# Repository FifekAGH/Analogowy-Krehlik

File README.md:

# Wstępny podział 

Krzysztof - frontend

Dominik - STM32F3 + decoupling, pullupy/downy itp

Filip - LDO, Układ odwracający napięcie, USB,Diody LED :)

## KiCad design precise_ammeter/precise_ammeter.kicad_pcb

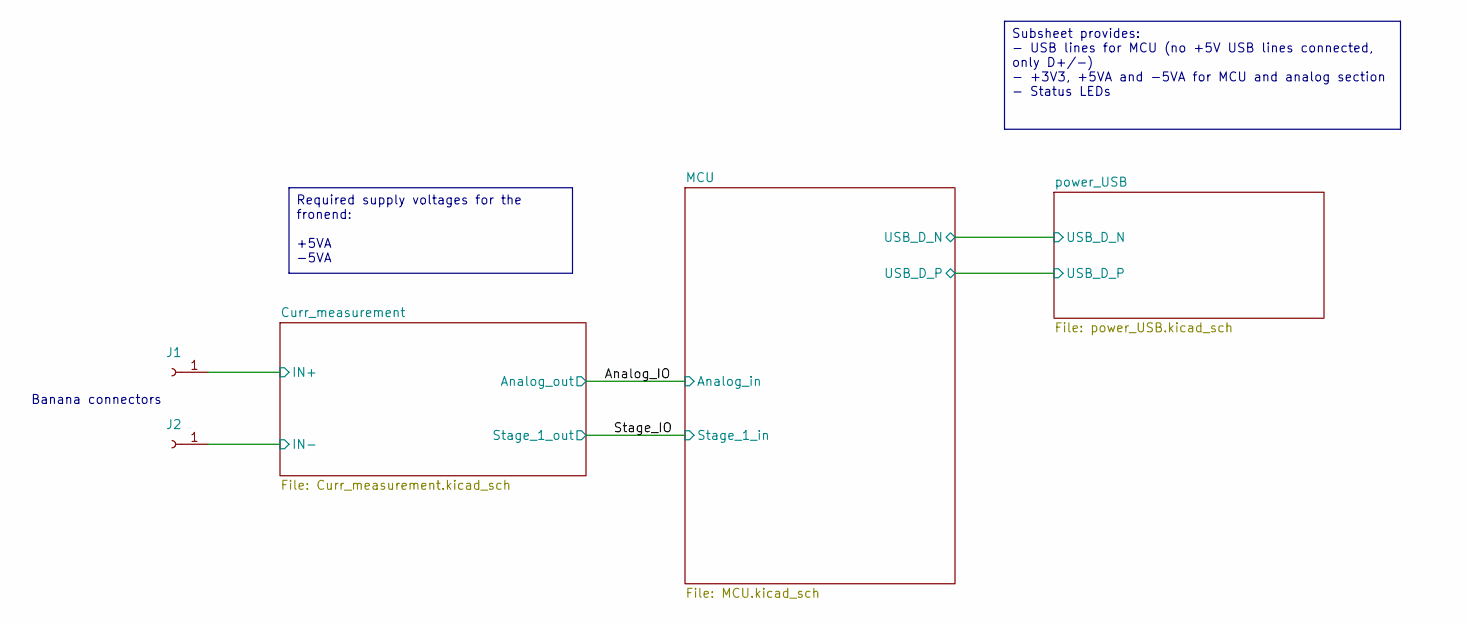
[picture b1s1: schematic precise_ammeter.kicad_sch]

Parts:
J1, J2: Conn_01x01_Socket; Banana_Jack_1Pin

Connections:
/Curr_measurement/IN+: J1.1; also elsewhere on the board
/Curr_measurement/IN-: J2.1; also elsewhere on the board

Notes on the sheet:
Banana connectors
Required supply voltages for the fronend: +5VA -5VA
Subsheet provides: - USB lines for MCU (no +5V USB lines connected, only D+/-) - +3V3, +5VA and -5VA for MCU and analog section - Status LEDs

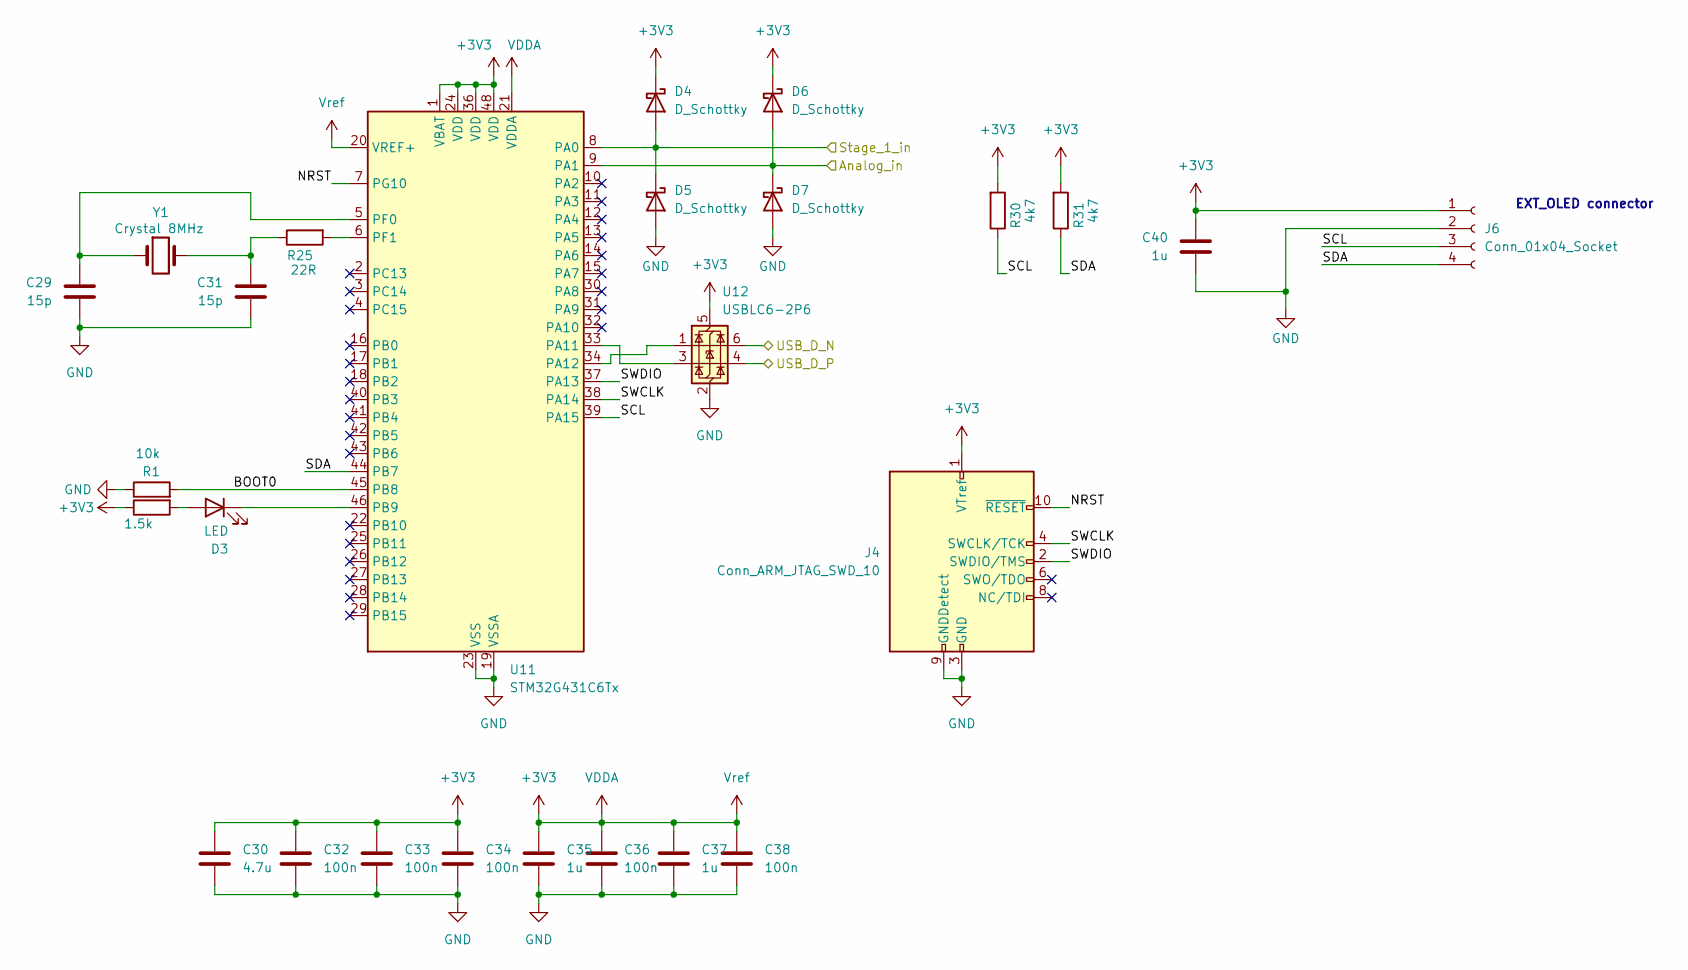
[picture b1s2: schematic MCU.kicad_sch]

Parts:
C29, C31: 15p; C_0805_2012Metric
C30: 4.7u; C_0805_2012Metric
C32, C33, C34, C36, C38: 100n; C_0805_2012Metric
C35, C37, C40: 1u; C_0805_2012Metric
D3: LED; LED_0805_2012Metric
D4, D5, D6, D7: D_Schottky; D_SOD-123F
J4: Conn_ARM_JTAG_SWD_10; PinHeader_2x05_P1.27mm_Vertical
J6: Conn_01x04_Socket; PinSocket_1x04_P2.54mm_Vertical
R1: 10k; R_0805_2012Metric_Pad1.20x1.40mm_HandSolder
R5: 1.5k; R_0805_2012Metric_Pad1.20x1.40mm_HandSolder
R25: 22R; R_0805_2012Metric_Pad1.20x1.40mm_HandSolder
R30, R31: 4k7; R_0805_2012Metric_Pad1.20x1.40mm_HandSolder
U11: STM32G431C6Tx; LQFP-48_7x7mm_P0.5mm
U12: USBLC6-2P6; SOT-666
Y1: Crystal 8MHz; Crystal_SMD_HC49-SD

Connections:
+3V3: C30.1, C32.1, C33.1, C34.1, C35.1, C36.1, C37.1, C38.1, C40.1, D4.1 (K), D6.1 (K), J4.1 (VTref), J6.1, R5.1, R30.2, R31.2, U11.1 (VBAT), U11.20 (VREF+), U11.21 (VDDA), U11.24 (VDD), U11.36 (VDD), U11.48 (VDD), U12.5 (VBUS); also elsewhere on the board
/Analog_IO: D6.2 (A), D7.1 (K), U11.9 (PA1); also elsewhere on the board
/MCU/BOOT0: R1.2, U11.45 (PB8)
/MCU/NRST: J4.10 (~RESET), U11.7 (PG10)
/MCU/SCL: J6.3, R30.1, U11.39 (PA15)
/MCU/SDA: J6.4, R31.1, U11.44 (PB7)
/MCU/SWCLK: J4.4 (SWCLK/TCK), U11.38 (PA14)
/MCU/SWDIO: J4.2 (SWDIO/TMS), U11.37 (PA13)
/MCU/USB_D_N: U12.6 (I/O1); also elsewhere on the board
/MCU/USB_D_P: U12.4 (I/O2); also elsewhere on the board
/Stage_IO: D4.2 (A), D5.1 (K), U11.8 (PA0); also elsewhere on the board
GND: C29.2, C30.2, C31.2, C32.2, C33.2, C34.2, C35.2, C36.2, C37.2, C38.2, C40.2, D5.2 (A), D7.2 (A), J4.3 (GND), J4.5 (GND), J4.9 (GNDDetect), J6.2, R1.1, U11.19 (VSSA), U11.23 (VSS), U11.35 (VSS), U11.47 (VSS), U12.2 (GND); also elsewhere on the board
unnamed: C31.1, R25.1, Y1.2
unnamed: D3.2 (A), R5.2
unnamed: D3.1 (K), U11.46 (PB9)
unnamed: U11.33 (PA11), U12.3 (I/O2)
unnamed: U11.34 (PA12), U12.1 (I/O1)
unnamed: C29.1, U11.5 (PF0), Y1.1
unnamed: R25.2, U11.6 (PF1)

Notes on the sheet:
EXT_OLED connector

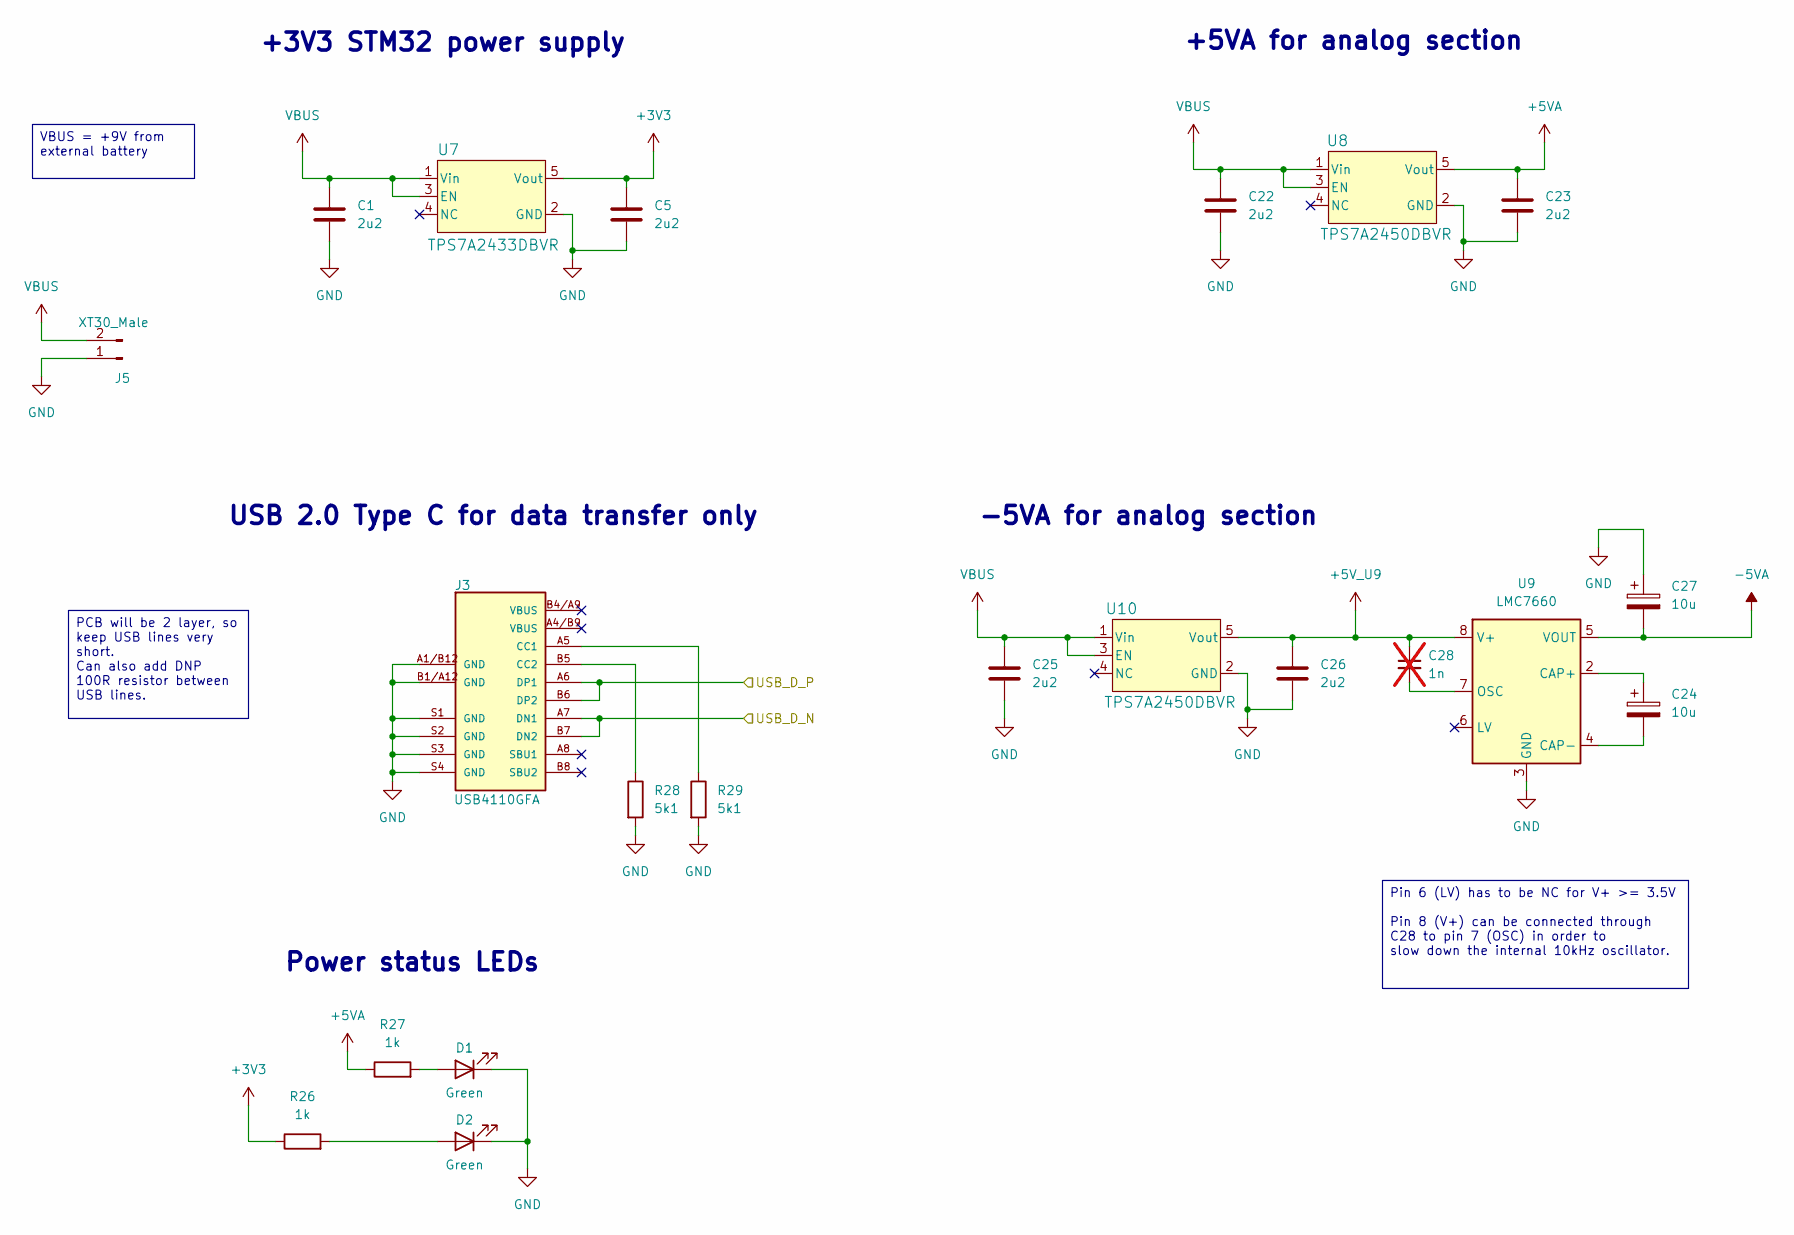
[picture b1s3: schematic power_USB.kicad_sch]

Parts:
C1, C5, C22, C23, C25, C26: 2u2; C_0805_2012Metric_Pad1.18x1.45mm_HandSolder; DC rating min. 25V
C24, C27: 10u; CP_Elec_4x5.4
C28: 1n; C_0805_2012Metric_Pad1.18x1.45mm_HandSolder; not fitted
D1, D2: Green; LED_0805_2012Metric_Pad1.15x1.40mm_HandSolder
J3: USB4110GFA; GCT_USB4110GFA
J5: XT30_Male; AMASS_XT30UPB-M_1x02_P5.0mm_Vertical
R26, R27: 1k; R_0805_2012Metric_Pad1.20x1.40mm_HandSolder
R28, R29: 5k1; R_0805_2012Metric_Pad1.20x1.40mm_HandSolder
U7: TPS7A2433DBVR; SOT23_DBV_TEX
U8, U10: TPS7A2450DBVR; SOT23_DBV_TEX
U9: LMC7660; SOIC-8_3.9x4.9mm_P1.27mm

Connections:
+3V3: C5.1, R26.1, U7.5 (Vout); also elsewhere on the board
+5VA: C23.1, R27.1, U8.5 (Vout); also elsewhere on the board
+5V_U9: C26.1, C28.1, U9.8 (V+), U10.5 (Vout)
-5VA: C27.2, U9.5 (VOUT); also elsewhere on the board
/MCU/USB_D_N: J3.A7 (DN1), J3.B7 (DN2); also elsewhere on the board
/MCU/USB_D_P: J3.A6 (DP1), J3.B6 (DP2); also elsewhere on the board
GND: C1.2, C5.2, C22.2, C23.2, C25.2, C26.2, C27.1, D1.1 (K), D2.1 (K), J3.A1/B12 (GND), J3.B1/A12 (GND), J3.S1 (GND), J3.S2 (GND), J3.S3 (GND), J3.S4 (GND), J5.1, R28.2, R29.2, U7.2 (GND), U8.2 (GND), U9.3 (GND), U10.2 (GND); also elsewhere on the board
unnamed: D1.2 (A), R27.2
unnamed: D2.2 (A), R26.2
unnamed: J3.A5 (CC1), R29.1
unnamed: J3.B5 (CC2), R28.1
unnamed: C24.1, U9.2 (CAP+)
unnamed: C24.2, U9.4 (CAP-)
unnamed: C28.2, U9.7 (OSC)
VBUS: C1.1, C22.1, C25.1, J5.2, U7.1 (Vin), U7.3 (EN), U8.1 (Vin), U8.3 (EN), U10.1 (Vin), U10.3 (EN)

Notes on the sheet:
-5VA for analog section
+3V3 STM32 power supply
Power status LEDs
+5VA for analog section
USB 2.0 Type C for data transfer only
VBUS = +9V from external battery
PCB will be 2 layer, so keep USB lines very short. Can also add DNP 100R resistor between USB lines.
Pin 6 (LV) has to be NC for V+ >= 3.5V Pin 8 (V+) can be connected through C28 to pin 7 (OSC) in order to slow down the internal 10kHz oscillator.

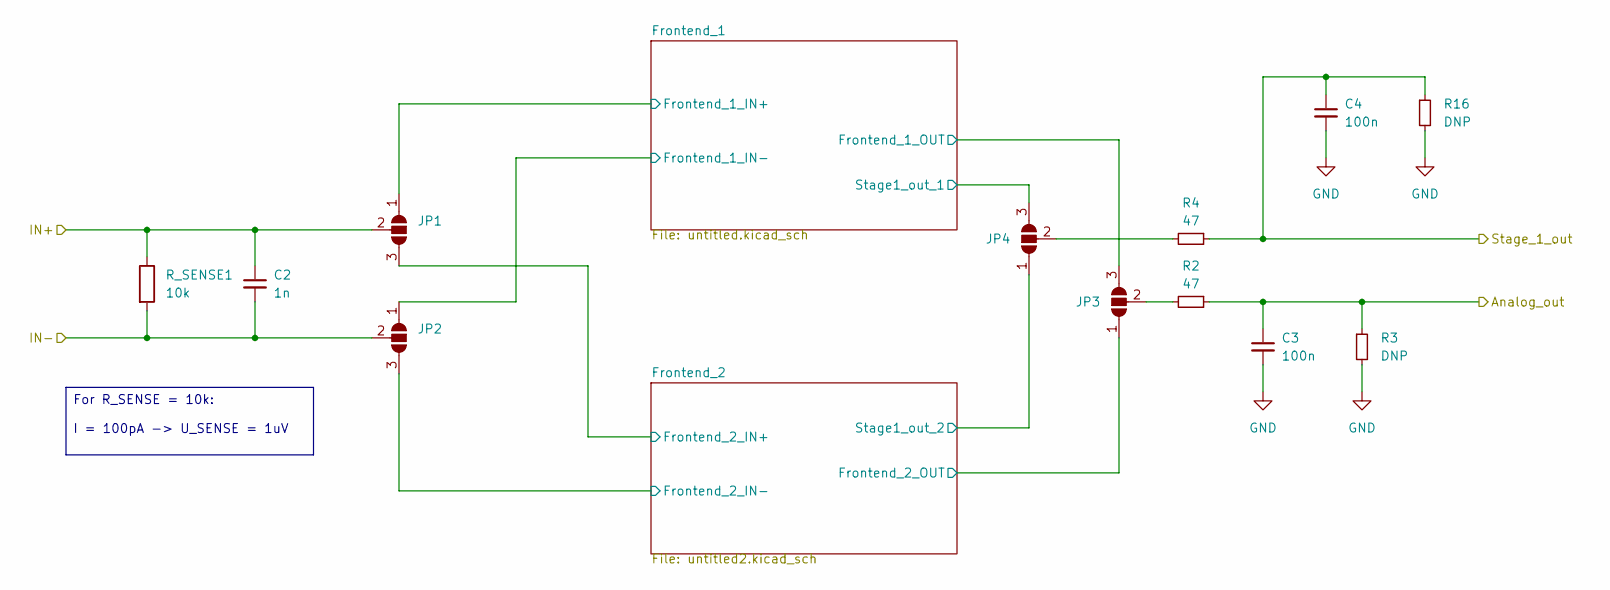
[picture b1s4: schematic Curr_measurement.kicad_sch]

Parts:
C2: 1n; C_0805_2012Metric_Pad1.18x1.45mm_HandSolder
C3, C4: 100n; C_0805_2012Metric_Pad1.18x1.45mm_HandSolder
JP1, JP2, JP3, JP4: SolderJumper_3_Open; SolderJumper-3_P1.3mm_Open_Pad1.0x1.5mm
R2, R4: 47; R_0805_2012Metric_Pad1.20x1.40mm_HandSolder
R3, R16: DNP; R_0805_2012Metric_Pad1.20x1.40mm_HandSolder
R_SENSE1: 10k; R_1206_3216Metric_Pad1.30x1.75mm_HandSolder

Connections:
/Analog_IO: C3.1, R2.1, R3.1; also elsewhere on the board
/Curr_measurement/Frontend_1/Frontend_1_IN+: JP1.1 (A); also elsewhere on the board
/Curr_measurement/Frontend_1/Frontend_1_IN-: JP2.1 (A); also elsewhere on the board
/Curr_measurement/Frontend_1/Frontend_1_OUT: JP3.3 (B); also elsewhere on the board
/Curr_measurement/Frontend_1/Stage1_out_1: JP4.3 (B); also elsewhere on the board
/Curr_measurement/Frontend_2/Frontend_2_IN+: JP1.3 (B); also elsewhere on the board
/Curr_measurement/Frontend_2/Frontend_2_IN-: JP2.3 (B); also elsewhere on the board
/Curr_measurement/Frontend_2/Frontend_2_OUT: JP3.1 (A); also elsewhere on the board
/Curr_measurement/Frontend_2/Stage1_out_2: JP4.1 (A); also elsewhere on the board
/Curr_measurement/IN+: C2.1, JP1.2 (C), R_SENSE1.1; also elsewhere on the board
/Curr_measurement/IN-: C2.2, JP2.2 (C), R_SENSE1.2; also elsewhere on the board
/Stage_IO: C4.1, R4.1, R16.1; also elsewhere on the board
GND: C3.2, C4.2, R3.2, R16.2; also elsewhere on the board
unnamed: JP3.2 (C), R2.2
unnamed: JP4.2 (C), R4.2

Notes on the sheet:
For R_SENSE = 10k: I = 100pA -> U_SENSE = 1uV

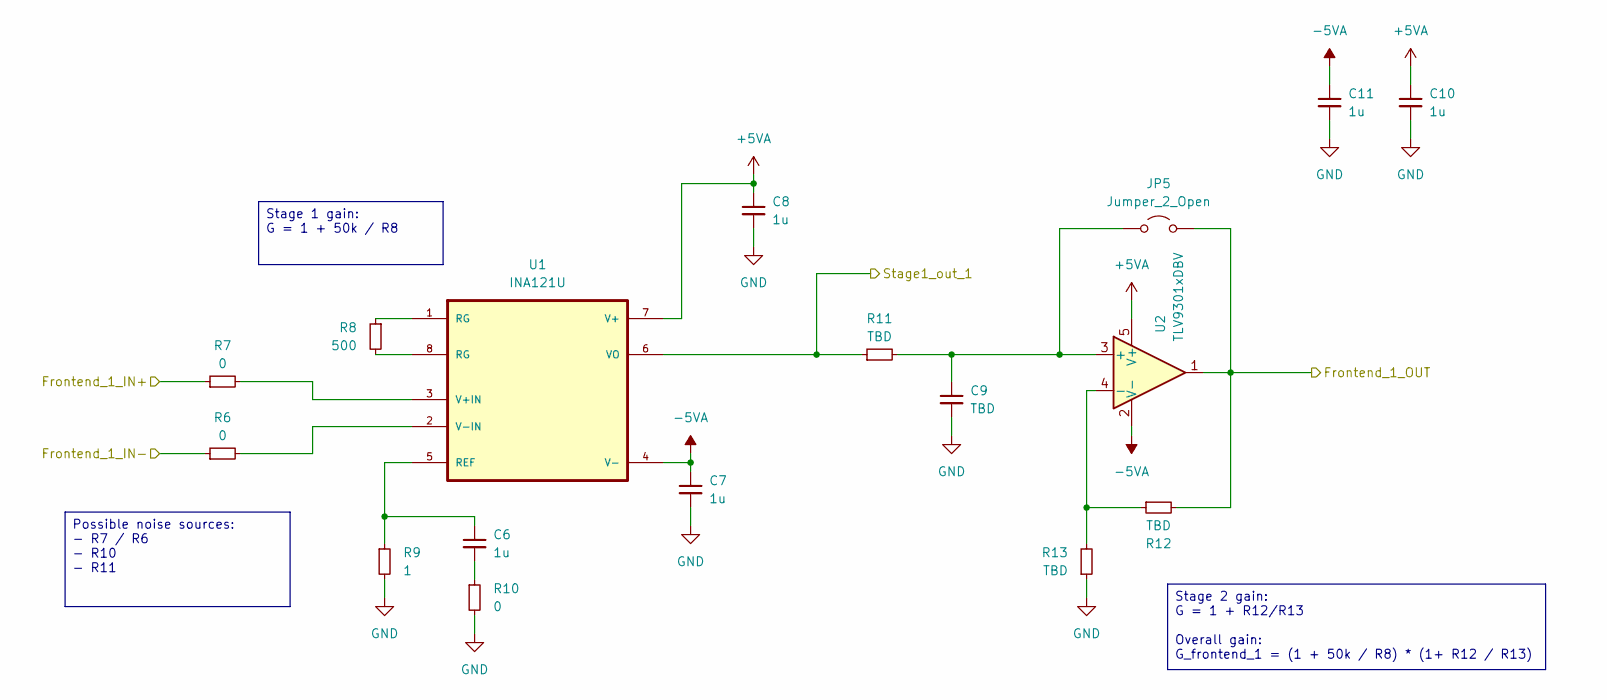
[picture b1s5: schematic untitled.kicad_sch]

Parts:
C6, C7, C8, C10, C11: 1u; C_0805_2012Metric_Pad1.18x1.45mm_HandSolder
C9: TBD; C_0805_2012Metric_Pad1.18x1.45mm_HandSolder
JP5: Jumper_2_Open; SolderJumper-2_P1.3mm_Open_Pad1.0x1.5mm
R6, R7, R10: 0; R_0805_2012Metric_Pad1.20x1.40mm_HandSolder
R8: 500; R_0805_2012Metric_Pad1.20x1.40mm_HandSolder
R9: 1; R_0805_2012Metric_Pad1.20x1.40mm_HandSolder
R11, R12, R13: TBD; R_0805_2012Metric_Pad1.20x1.40mm_HandSolder
U1: INA121U; DIP-8_W7.62mm_LongPads
U2: TLV9301xDBV; SOT-23-5

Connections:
+5VA: C8.1, C10.1, U1.7 (V+), U2.5 (V+); also elsewhere on the board
-5VA: C7.1, C11.1, U1.4 (V-), U2.2 (V-); also elsewhere on the board
/Curr_measurement/Frontend_1/Frontend_1_IN+: R7.1; also elsewhere on the board
/Curr_measurement/Frontend_1/Frontend_1_IN-: R6.1; also elsewhere on the board
/Curr_measurement/Frontend_1/Frontend_1_OUT: JP5.2 (B), R12.2, U2.1; also elsewhere on the board
/Curr_measurement/Frontend_1/Stage1_out_1: R11.1, U1.6 (VO); also elsewhere on the board
GND: C7.2, C8.2, C9.2, C10.2, C11.2, R9.2, R10.2, R13.1; also elsewhere on the board
unnamed: C6.2, R10.1
unnamed: C9.1, JP5.1 (A), R11.2, U2.3 (+)
unnamed: R8.1, U1.1 (RG)
unnamed: R8.2, U1.8 (RG)
unnamed: C6.1, R9.1, U1.5 (REF)
unnamed: R7.2, U1.3 (V+IN)
unnamed: R6.2, U1.2 (V-IN)
unnamed: R12.1, R13.2, U2.4 (-)

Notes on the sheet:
Stage 1 gain: G = 1 + 50k / R8
Possible noise sources: - R7 / R6 - R10 - R11
Stage 2 gain: G = 1 + R12/R13 Overall gain: G_frontend_1 = (1 + 50k / R8) * (1+ R12 / R13)

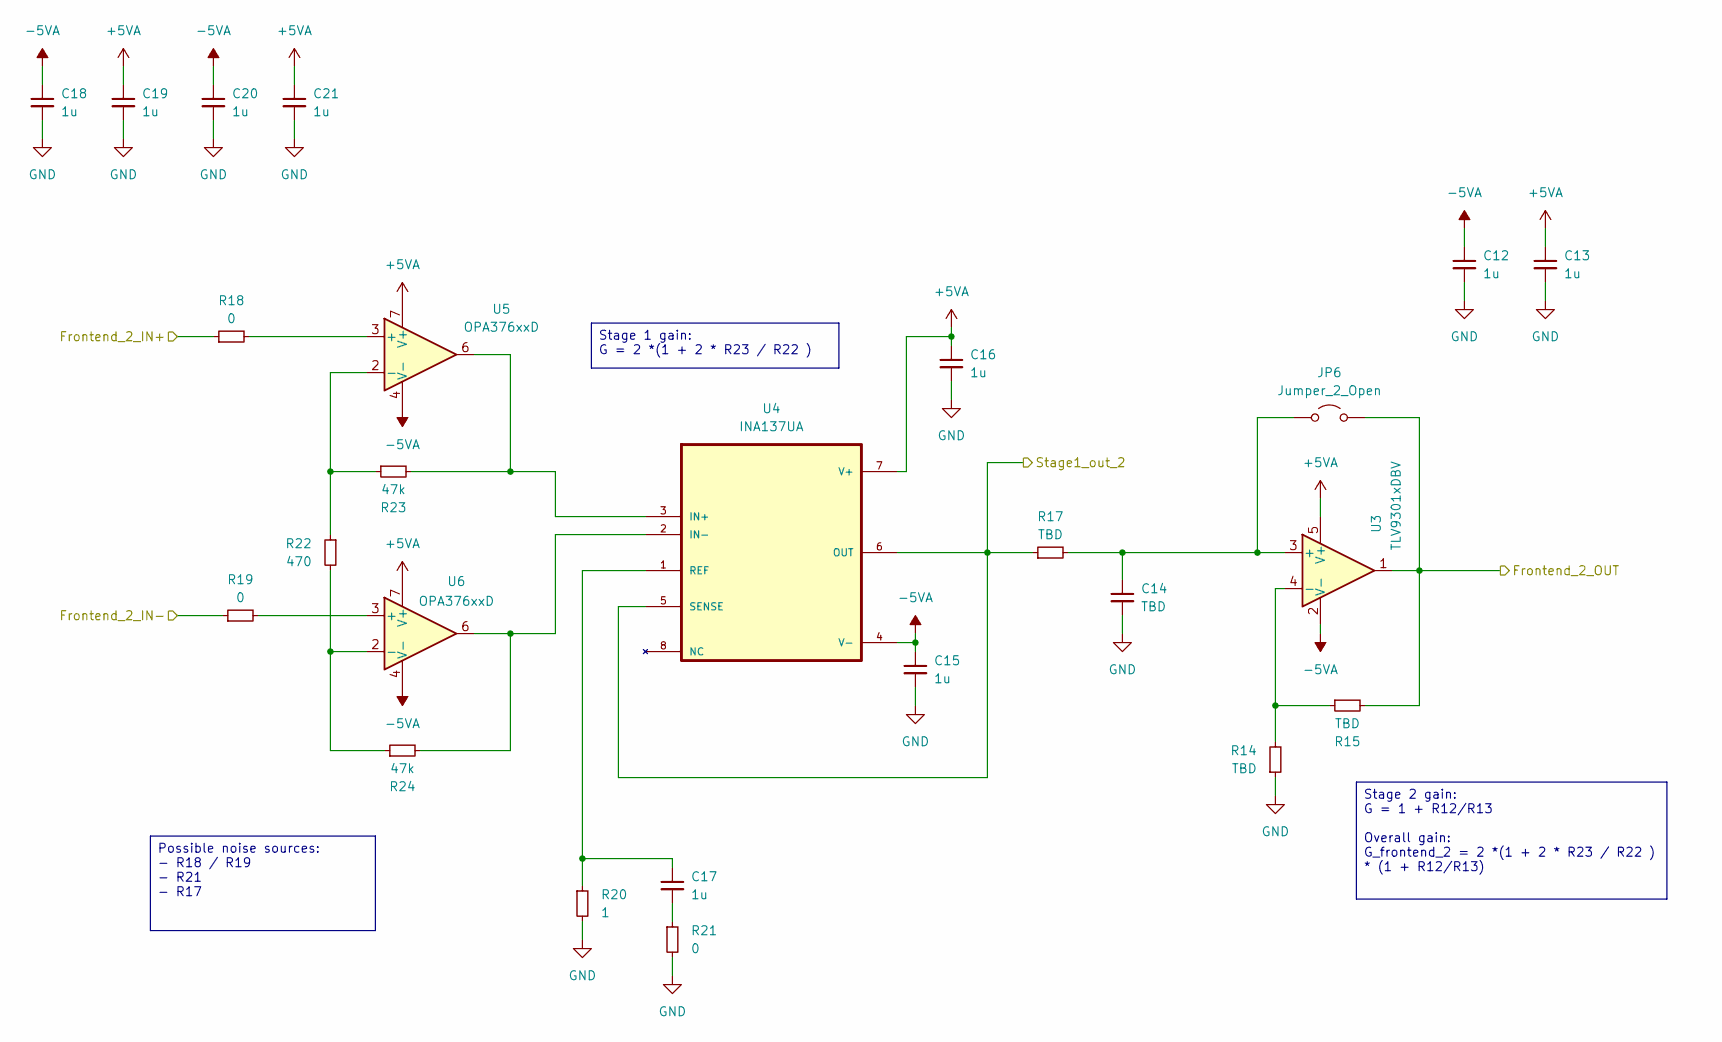
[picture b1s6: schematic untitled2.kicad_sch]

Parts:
C12, C13, C15, C16, C17, C18, C19, C20, C21: 1u; C_0805_2012Metric_Pad1.18x1.45mm_HandSolder
C14: TBD; C_0805_2012Metric_Pad1.18x1.45mm_HandSolder
JP6: Jumper_2_Open; SolderJumper-2_P1.3mm_Open_Pad1.0x1.5mm
R14, R15, R17: TBD; R_0805_2012Metric_Pad1.20x1.40mm_HandSolder
R18, R19, R21: 0; R_0805_2012Metric_Pad1.20x1.40mm_HandSolder
R20: 1; R_0805_2012Metric_Pad1.20x1.40mm_HandSolder
R22: 470; R_0805_2012Metric_Pad1.20x1.40mm_HandSolder
R23, R24: 47k; R_0805_2012Metric_Pad1.20x1.40mm_HandSolder
U3: TLV9301xDBV; SOT-23-5
U4: INA137UA; SOIC127P599X175-8N
U5, U6: OPA376xxD; SOIC-8_3.9x4.9mm_P1.27mm

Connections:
+5VA: C13.1, C16.1, C19.1, C21.1, U3.5 (V+), U4.7 (V+), U5.7 (V+), U6.7 (V+); also elsewhere on the board
-5VA: C12.1, C15.1, C18.1, C20.1, U3.2 (V-), U4.4 (V-), U5.4 (V-), U6.4 (V-); also elsewhere on the board
/Curr_measurement/Frontend_2/Frontend_2_IN+: R18.1; also elsewhere on the board
/Curr_measurement/Frontend_2/Frontend_2_IN-: R19.1; also elsewhere on the board
/Curr_measurement/Frontend_2/Frontend_2_OUT: JP6.2 (B), R15.2, U3.1; also elsewhere on the board
/Curr_measurement/Frontend_2/Stage1_out_2: R17.1, U4.5 (SENSE), U4.6 (OUT); also elsewhere on the board
GND: C12.2, C13.2, C14.2, C15.2, C16.2, C18.2, C19.2, C20.2, C21.2, R14.1, R20.2, R21.2; also elsewhere on the board
unnamed: C17.2, R21.1
unnamed: C14.1, JP6.1 (A), R17.2, U3.3 (+)
unnamed: R14.2, R15.1, U3.4 (-)
unnamed: R23.2, U4.3 (IN+), U5.6
unnamed: R24.2, U4.2 (IN-), U6.6
unnamed: C17.1, R20.1, U4.1 (REF)
unnamed: R18.2, U5.3 (+)
unnamed: R22.1, R23.1, U5.2 (-)
unnamed: R19.2, U6.3 (+)
unnamed: R22.2, R24.1, U6.2 (-)

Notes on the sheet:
Stage 2 gain: G = 1 + R12/R13 Overall gain: G_frontend_2 = 2 *(1 + 2 * R23 / R22 ) * (1 + R12/R13)
Possible noise sources: - R18 / R19 - R21 - R17
Stage 1 gain: G = 2 *(1 + 2 * R23 / R22 )

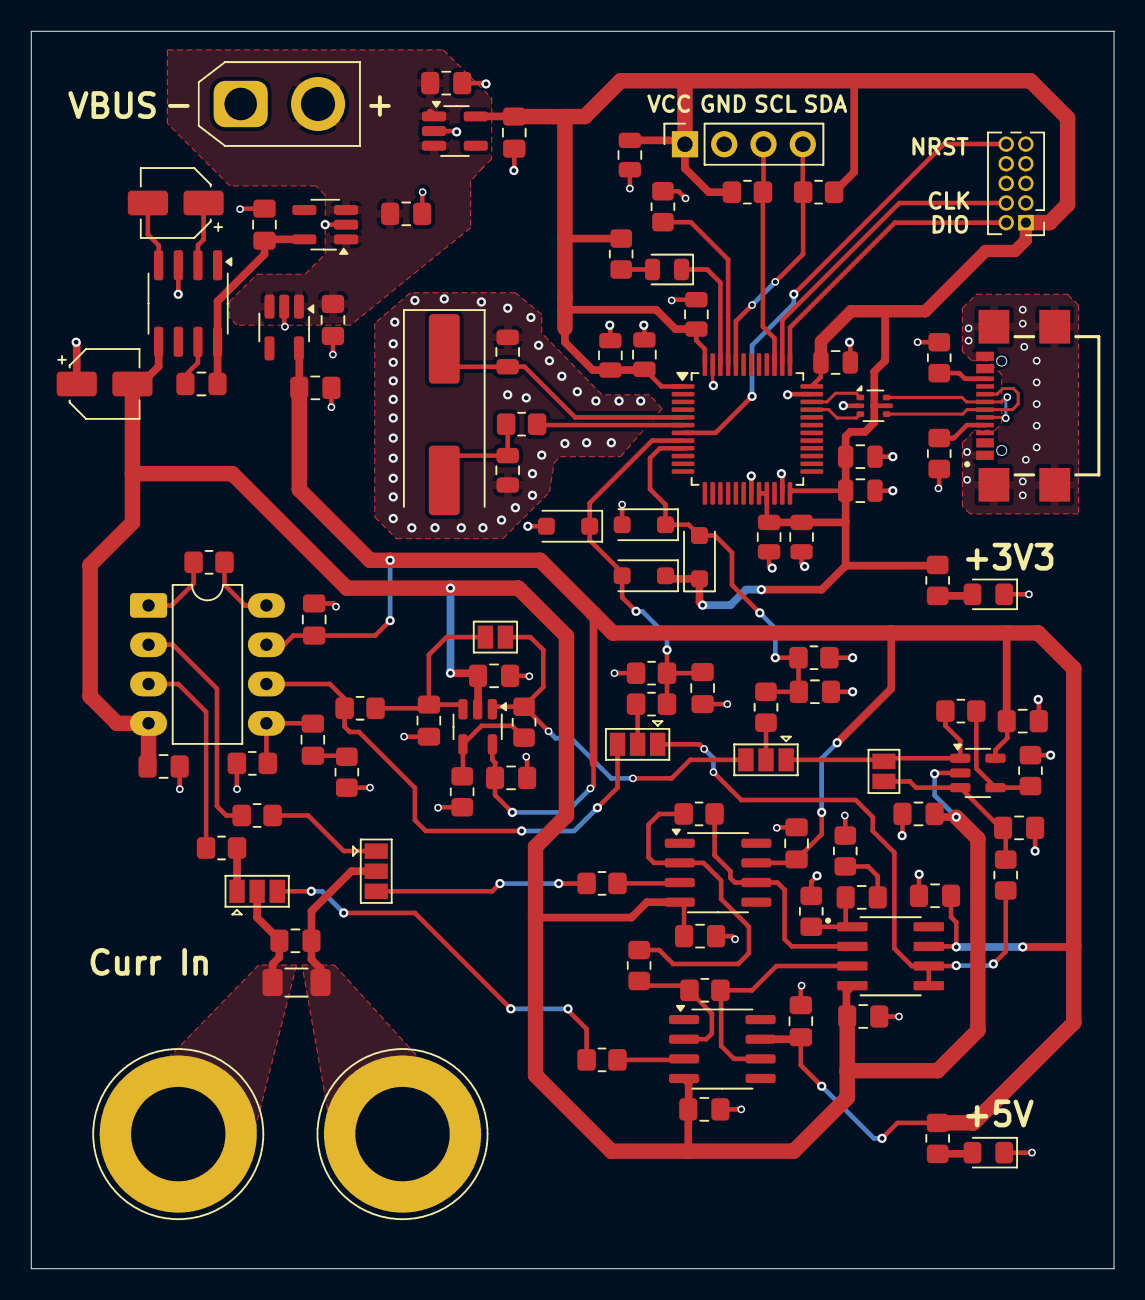
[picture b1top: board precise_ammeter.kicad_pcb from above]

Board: 2 copper layers, 70.0 x 80.0 mm, 103 parts (0 on the bottom side), 60 nets.

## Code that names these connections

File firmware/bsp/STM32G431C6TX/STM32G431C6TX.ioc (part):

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Mcu.Name=STM32G431C(6-8-B)Tx
Mcu.Package=LQFP48
Mcu.UserName=STM32G431C6Tx
PA0.Signal=ADC1_IN1
PA1.GPIOParameters=GPIO_Mode
PA1.GPIO_Mode=GPIO_MODE_ANALOG
PA1.Mode=IN2-Single-Ended
PA1.Signal=ADC1_IN2
PA15.Mode=I2C
PA15.Signal=I2C1_SCL
PB7.Mode=I2C
PB7.Signal=I2C1_SDA
PB9.GPIOParameters=GPIO_Label
PB9.GPIO_Label=LED
PB9.Signal=GPIO_Output
PF0-OSC_IN.Mode=HSE-External-Oscillator
PF0-OSC_IN.Signal=RCC_OSC_IN
PF1-OSC_OUT.Mode=HSE-External-Oscillator
PF1-OSC_OUT.Signal=RCC_OSC_OUT
RCC.HSE_VALUE=8000000
RCC.SYSCLKFreq_VALUE=170000000
RCC.SYSCLKSource=RCC_SYSCLKSOURCE_PLLCLK
board=custom

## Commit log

2025-10-28 Stworzony projekt KiCad 9.Utworzone 3 sheety hierarchiczne do podzialu
2025-11-01 Dodano schemat frontend_1
2025-11-02 Dodano drugi schemat frontendu
2025-11-03 Dodano Sekcje zasilanie MCU i wzmacniaczy oraz konektor USB
2025-11-03 added mcu part
2025-11-03 dodano rezystory do diod LED
2025-11-03 Dodane pull down na piny CC USB
2025-11-03 fixed mcu schematic
2025-11-03 Dodano konektor XT30 dla baterii i zrobiono adnotacj diod Schotkiego na schemacie MCU
2025-11-04 dodano layout
2025-11-04 dodano pdf ze schematem
2025-11-04 dodano skonczone PCB
2025-11-08 adding 1 more 10u cap at voltage inverter
2025-11-08 adding OLED display
2025-11-08 Corrected all footprints before starting layout
2025-11-08 added step model for xt30
2025-11-08 layout started
2025-11-08 USB layout
2025-11-09 placement finished
2025-11-09 placement changed
2025-11-09 jebane gowno
2025-11-09 layout almost done. Need to connect Curr_in and fix warnings
2025-11-09 Layout Done, DRC done
2025-11-09 dodane teardrops
2025-11-12 przesunieto konektory LCD i SWD. Przesunieto diode LED 3v3
2025-11-15 dodano warrtosci elementow w frontend1
2025-12-20 unknown changes
2025-12-23 feat: another bsp target
2025-12-28 wip: add display driver
2025-12-31 feat: implemented main functionality
2026-01-01 feat: add bsp sources to target board
2026-01-02 fix: reverted liker script
2026-01-02 feat: initial firmware
2026-01-04 added compoennt values for frontend 2
2026-01-06 feat: configured oversampling
2026-01-09 feat: improve oversampling
2026-01-11 wip: adjust filtering to meet requirements
2026-01-11 feat: improve overall performance
2026-01-11 feat: add resolution to mA
